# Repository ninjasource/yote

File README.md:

# Yote - Year of the Ear

Experiments with the nrf5340 Audio Dk, CS47L63 DSP chip and Yote experimental hearing aid. 
For Rust firmware, open the `firmware` folder instead of working from this folder

## Prerequisites

`cargo install probe-rs --features="cli"`

If probe-rs does not work then a known working version can be found here:
https://github.com/probe-rs/probe-rs.git#ff2370fb

## To run

NOTE on naming:
All the examples prefixed with "yote" are for the custom built hearing aid device. Everything else is for the nRF5340 Audio-dk

IMPORTANT: be sure to set the appropriate runner in .cargo/config.toml

```
cargo run --bin blinky --release
```

## Troubleshooting

You may get an "Arm specific error at runtime and the most likely cause is that you ran probe-run with the `--erase-all` flag set.
Check the notes in `.cargo/config.toml`

Here are some commands you may find useful when working with the nrf5340 audio dk. 
You will need to install the nrfjprog command line tools from Nordic beforehand.

```
nrfjprog -i
nrfjprog --eraseall --snr 1050175639 (locks up)
nrfjprog --recover --coprocessor CP_APPLICATION --snr 1050175639
nrfjprog --recover --snr 1050175639 (same as application above)
nrfjprog --recover --coprocessor CP_NETWORK --snr 1050175639 (locks up)
```

Here is some code that you can use to flash the device without probe-run:

```
#! /usr/bin/env bash

cargo objcopy --release -- -O ihex test.hex
nrfjprog -f NRF53 --erasepage 0x00000000-0x00100000
nrfjprog -f NRF53 --program test.hex --debugreset
rm test.hex
```

## How it works

This demo uses the mcu to generate a tone and plays it into the cs47l63 dsp chip. 
Before it can do that it has to configure the dsp chip correctly by writing to various registers over spi.
There are multiple tasks running simultaneously so we need a mechanism to share the spi bus between them.

The demo runs three main tasks simultaneously: 
1. Handle interrupts from the DSP chip which indicates that long running tasks on the DSP have been completed
2. Handle button presses to control playback and volume
3. Generate a waveform in real time and push the data to the DSP chip over the I2S sound bus

## Project structure

The `cs47l63` cargo library is responsible for booting up the cs47l63 chip correctly and providing a bunch of register address and constants to be used by the application.
The `hw_dsp` (hardware digital signal processing) constrains a collection of helper functions that make calls to the `cs47l63` driver to configure it.
The `main.rs` application should use `dsp` module to exclusively communicate with the `cs47l63` even though, in theory, it could communicate directly with it through the `shared_bus` module. Right now there is some code duplication because of some power saving experiments where we need to drop the spi bus after every use. The duplicated code should be consolidated as soon as an acceptable abstraction has been designed.

## Chapro compilation

CC=arm-none-eabi-gcc
AR=arm-none-eabi-ar
CFLAGS = -W -Wall -Os -mthumb -ffunction-sections -fdata-sections -mcpu=cortex-m33 -DBR_ARMEL_CORTEXM_GCC -I$(INCDIR) -Wno-unused-local-typedef -fPIC -mfpu=fpv5-sp-d16 -mfloat-abi=hard

## Notes on Power Consumption

Here are some of the things that seem to affect power consumption:

Logging: No effect unless a debugger is attached - then huge effect
Core clock 64Mhz -> 128Mhz and Flash Cache enabled - 200uA consumption
Setting all peripheral pins to Input Low on startup - no effect, they seem to already default to their lowest power setting anyway

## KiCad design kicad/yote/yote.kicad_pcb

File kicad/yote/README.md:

# Kicad project for schematic and PCB

Requires Kicad 8.0
Step files for the 3D rendering of the board will be checked in soon but at the moment they are not in the project path and therefore not rendered correctly. 
This messes up the PCB Design Rule checker too. Kicad projects are a little tricky to setup to work on multiple machines because of all the internal and external library files involved. 

If you do not have the correct version of Kicad installed then you can use the exported PDF schematic below:

Please see output/yote.pdf for now

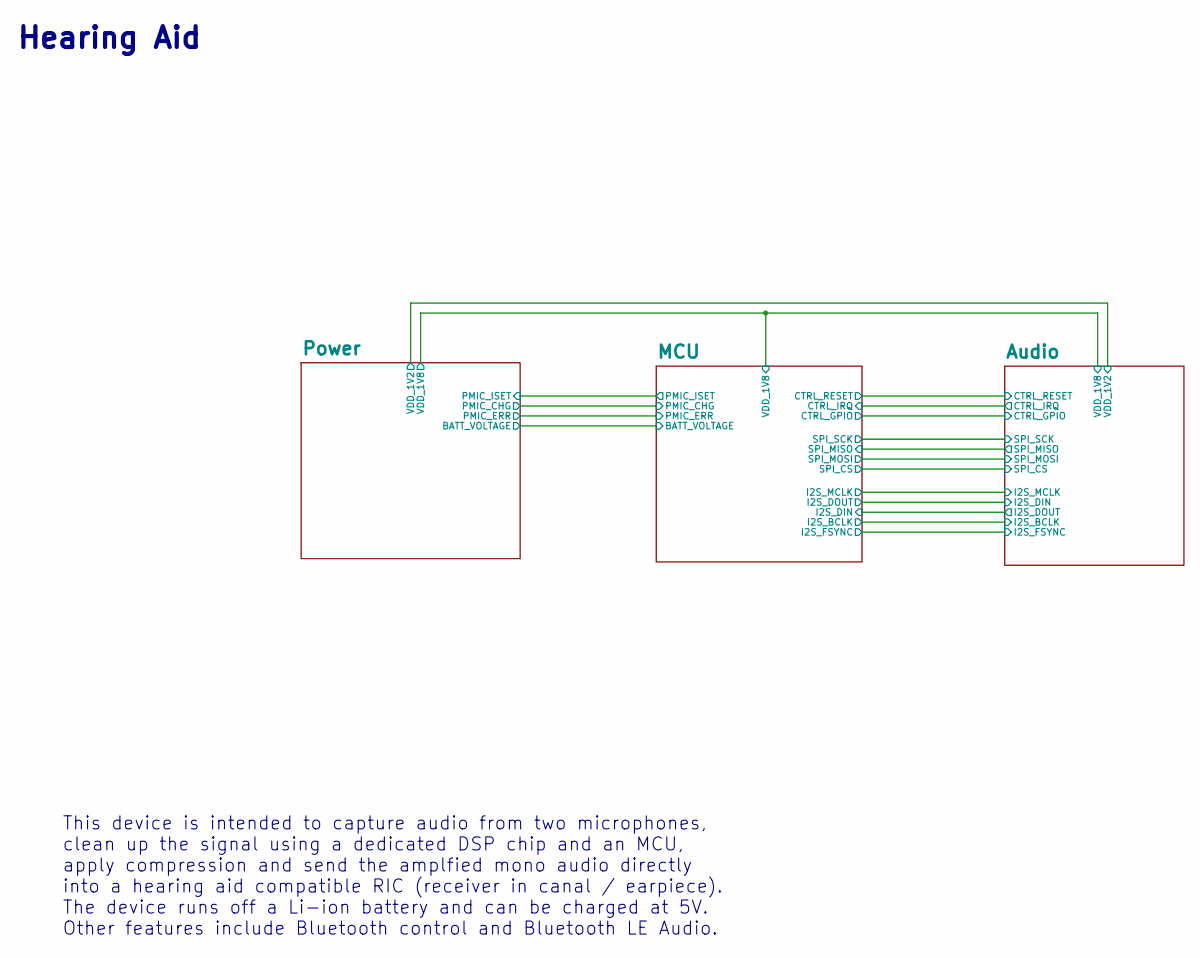
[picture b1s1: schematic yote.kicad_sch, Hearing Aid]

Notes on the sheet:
Hearing Aid
This device is intended to capture audio from two microphones, clean up the signal using a dedicated DSP chip and an MCU, apply compression and send the amplfied mono audio directly into a hearing aid compatible RIC (receiver in canal / earpiece). The device runs off a Li-ion battery and can be cha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

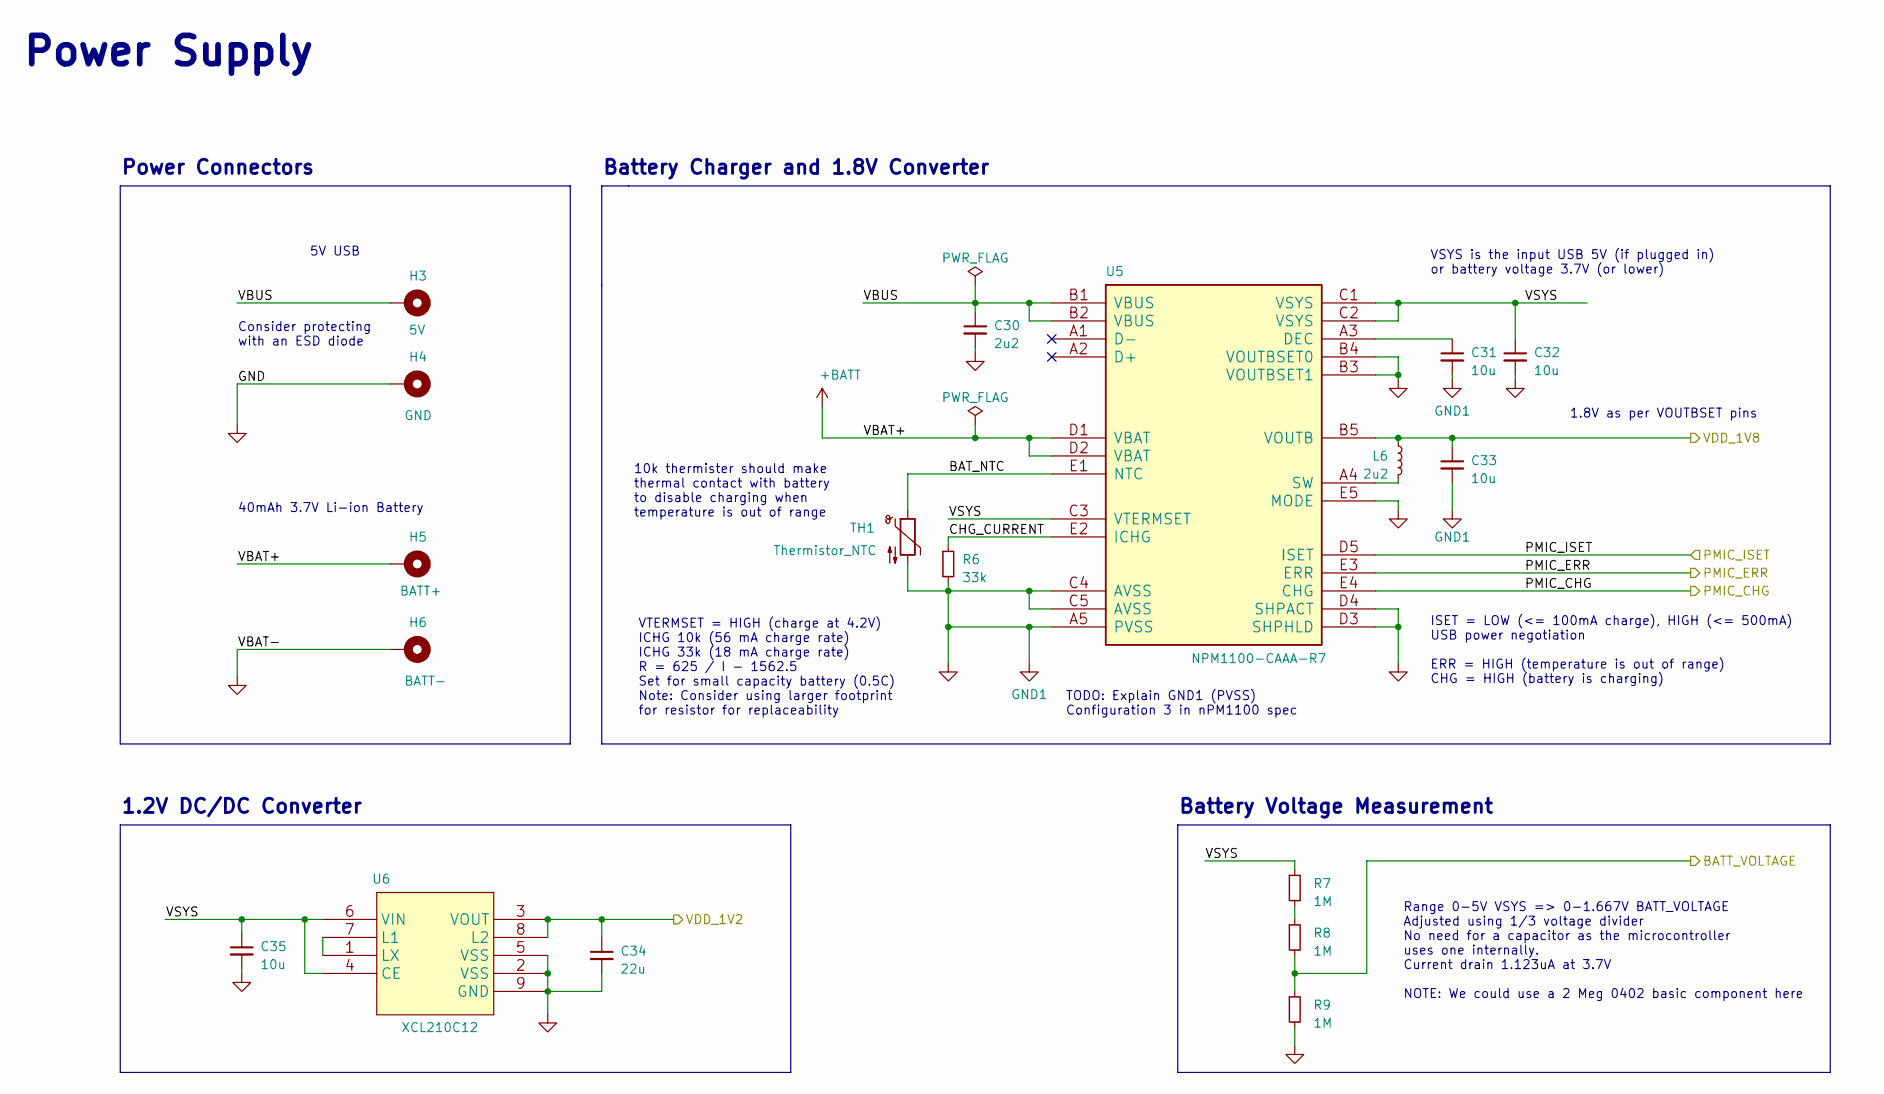
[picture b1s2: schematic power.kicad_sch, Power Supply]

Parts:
C30: 2u2; C_0402_1005Metric_Square; Mfg Part # GRM155R61A225KE95D
C31, C32, C33, C35: 10u; C_0603_1608Metric_Square; Mfg Part # GRM188R61A106KE69D
C34: 22u; C_0603_1608Metric_Square; Mfg Part # GRM188R61A226ME15D
H3: 5V; MountingHole_0.6mm_Pad_TopBottom
H4: GND; MountingHole_0.6mm_Pad_TopBottom
H5: BATT+; MountingHole_0.6mm_Pad_TopBottom
H6: BATT-; MountingHole_0.6mm_Pad_TopBottom
L6: 2u2; L_0603_1608Metric_MLZ1608M100WTD25; Mfg Part # MLP1608H2R2BT0S1
R6: 33k; R_0603_1608Metric_Square; Mfg Part # 0603WAF3302T5E
R7, R8, R9: 1M; R_0201_0603Metric_Square; Mfg Part # RC0201FR-071ML
TH1: Thermistor_NTC; R_0402_1005Metric_Square; Mfg Part # NCU15XH103F6SRC
U5: NPM1100-CAAA-R7; PARTREV V1.0
U6: XCL210C12; Mfg Part # XCL210C121GR-G

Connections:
+1V8: C33.1, L6.2, U5.B5 (VOUTB); also elsewhere on the board
+BATT: H5.1, U5.D1 (VBAT), U5.D2 (VBAT); also elsewhere on the board
/Audio/VDD_1V2: C34.1, U6.3 (VOUT), U6.8 (L2); also elsewhere on the board
/MCU/BATT_VOLTAGE: R8.2, R9.1; also elsewhere on the board
/MCU/PMIC_CHG: U5.E4 (CHG); also elsewhere on the board
/MCU/PMIC_ERR: U5.E3 (ERR); also elsewhere on the board
/MCU/PMIC_ISET: U5.D5 (ISET); also elsewhere on the board
/Power/BAT_NTC: TH1.1, U5.E1 (NTC)
/Power/CHG_CURRENT: R6.1, U5.E2 (ICHG)
/Power/VBUS: C30.1, H3.1, U5.B1 (VBUS), U5.B2 (VBUS)
/Power/VSYS: C32.1, C35.1, R7.1, U5.C1 (VSYS), U5.C2 (VSYS), U5.C3 (VTERMSET), U6.4 (CE), U6.6 (VIN)
GND: C30.2, C31.2, C32.2, C33.2, C34.2, C35.2, H4.1, H6.1, R6.2, R9.2, TH1.2, U5.A5 (PVSS), U5.B3 (VOUTBSET1), U5.B4 (VOUTBSET0), U5.C4 (AVSS), U5.C5 (AVSS), U5.D3 (SHPHLD), U5.D4 (SHPACT), U5.E5 (MODE), U6.2 (VSS), U6.5 (VSS), U6.9 (GND); also elsewhere on the board
unnamed: R7.2, R8.1
unnamed: C31.1, U5.A3 (DEC)
unnamed: L6.1, U5.A4 (SW)
unnamed: U6.1 (LX), U6.7 (L1)

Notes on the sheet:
VSYS is the input USB 5V (if plugged in) or battery voltage 3.7V (or lower)
Range 0-5V VSYS => 0-1.667V BATT_VOLTAGE Adjusted using 1/3 voltage divider No need for a capacitor as the microcontroller uses one internally. Current drain 1.123uA at 3.7V NOTE: We could use a 2 Meg 0402 basic component here
TODO: Explain GND1 (PVSS) Configuration 3 in nPM1100 spec
Battery Voltage Measurement
Battery Charger and 1.8V Converter
ISET = LOW (<= 100mA charge), HIGH (<= 500mA) USB power negotiation ERR = HIGH (temperature is out of range) CHG = HIGH (battery is charging)
1.2V DC/DC Converter
1.8V as per VOUTBSET pins
5V USB
Power Supply
40mAh 3.7V Li-ion Battery
Consider protecting with an ESD diode
VTERMSET = HIGH (charge at 4.2V) ICHG 10k (56 mA charge rate) ICHG 33k (18 mA charge rate) R = 625 / I - 1562.5 Set for small capacity battery (0.5C) Note: Consider using larger footprint for resistor for replaceability
Power Connectors
10k thermister should make thermal contact with battery to disable charging when temperature is out of range

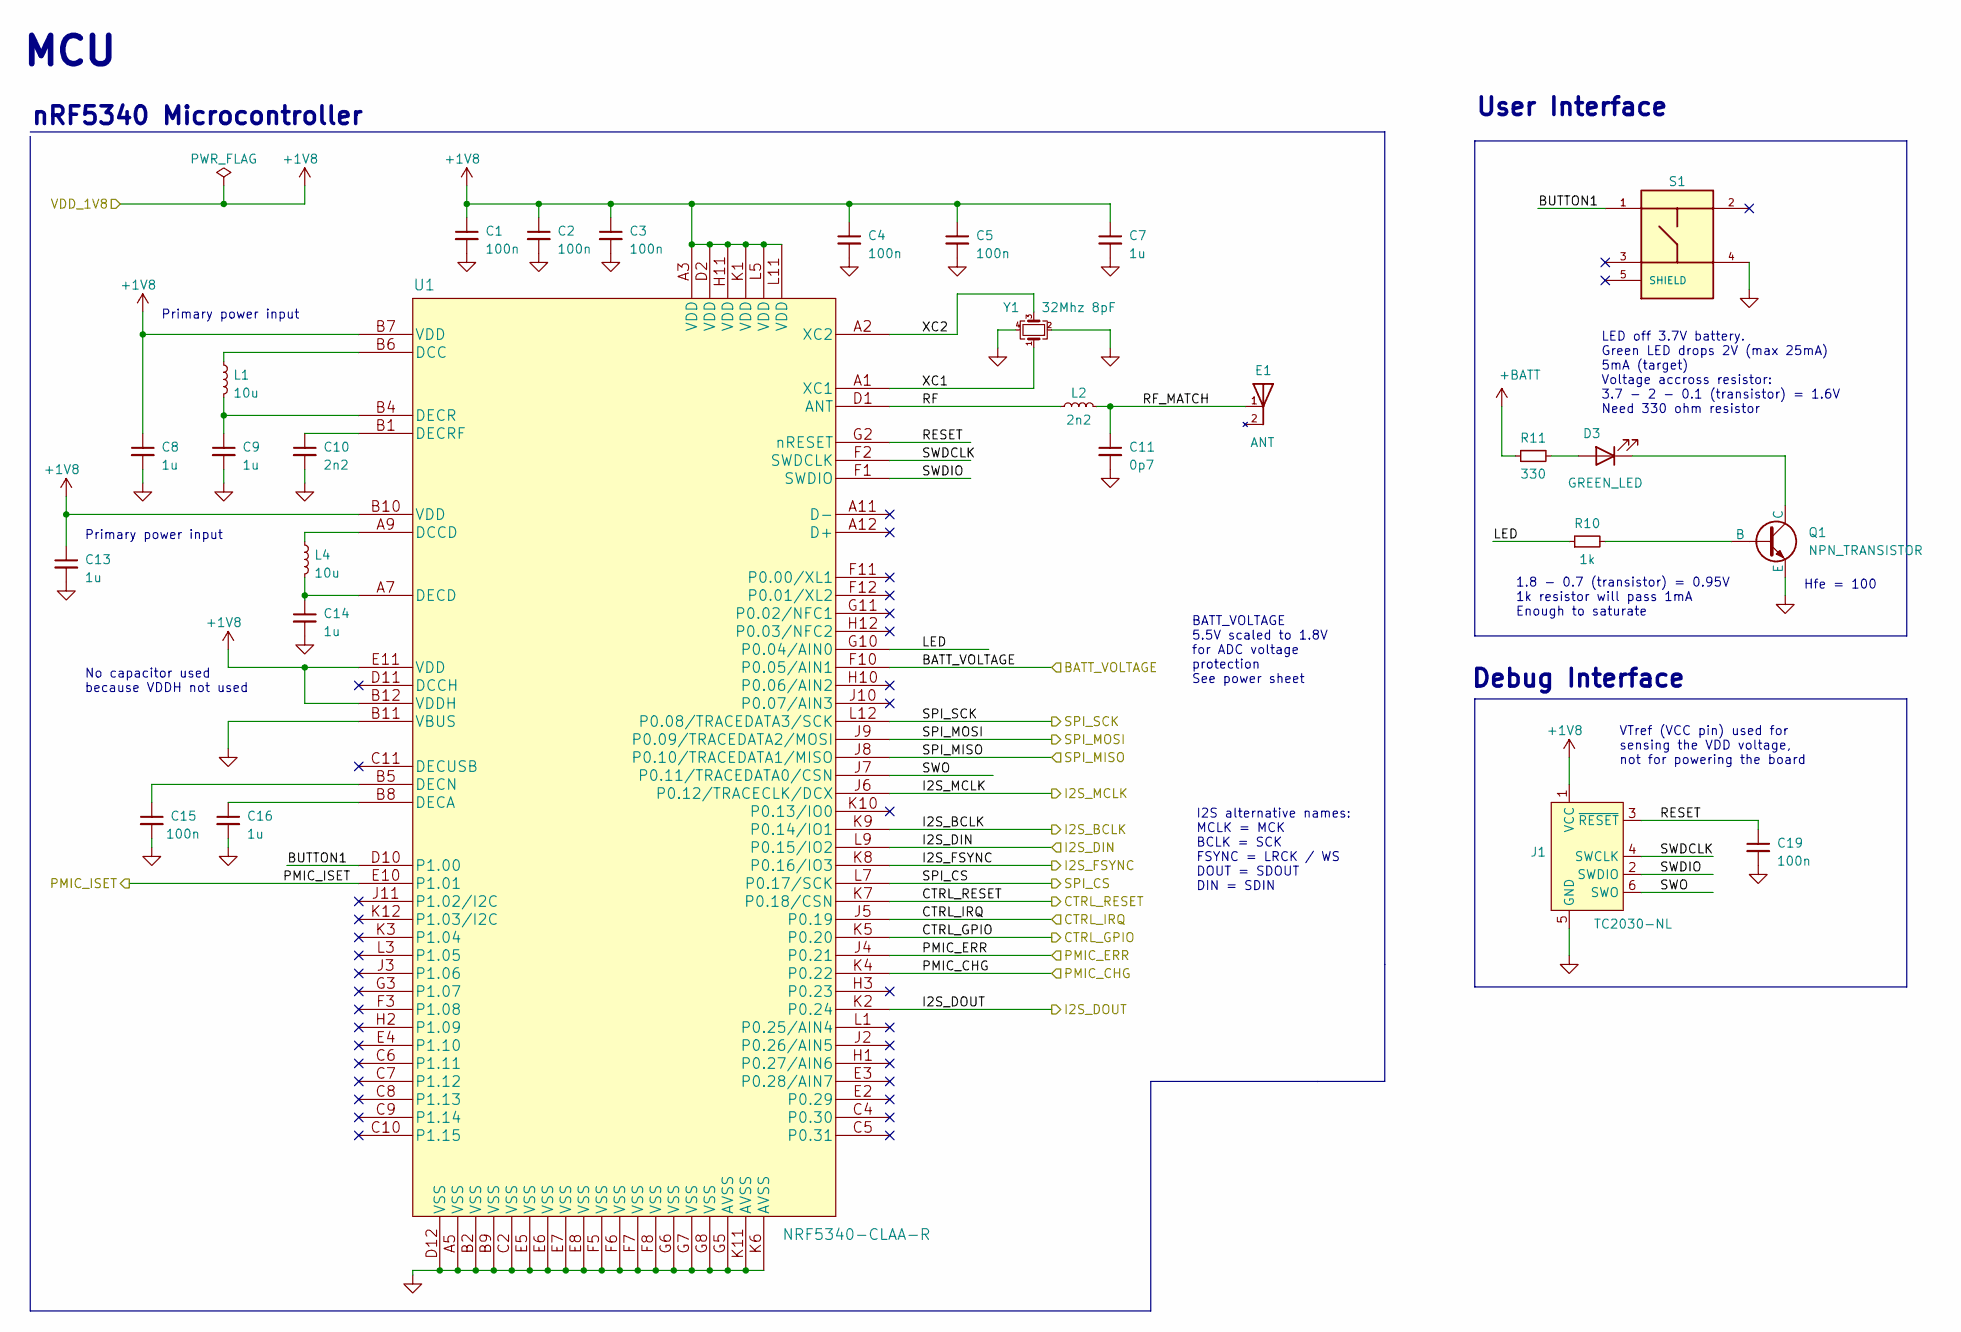
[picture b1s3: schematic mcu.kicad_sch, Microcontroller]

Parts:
C1, C2, C3, C4, C5, C15, C19: 100n; C_0201_0603Metric_Square; Mfg Part # GRM033R61A104KE15D
C7, C8, C9, C13, C14, C16: 1u; C_0402_1005Metric_Square; Mfg Part # GRM155R60J105KE19D
C10: 2n2; C_0201_0603Metric_Square; Mfg Part # GRM033R71A222KA01D
C11: 0p7; C_0201_0603Metric_Square; Mfg Part # GRM0335C1HR70WA01D
D3: GREEN_LED; LED_0402_1005Metric; Mfg Part # 16-213SYGC/S530-E3/TR8
E1: ANT; 2450AT18B100E; PARTREV 4.0
J1: TC2030-NL; Tag-Connect_TC2030-IDC-NL_2x03_P1.27mm_Vertical
L1, L4: 10u; L_0603_1608Metric_MLZ1608M100WTD25; Mfg Part # MLZ1608M100WTD25
L2: 2n2; L_0201_0603Metric_Square; Mfg Part # LQP03HQ2N2B02
Q1: NPN_TRANSISTOR; Npn_Transistor_TP5001P3; Mfg Part # TP5001P3
R10: 1k; R_0201_0603Metric_Square; Mfg Part # RC0201FR-071KL
R11: 330; R_0201_0603Metric_Square; Mfg Part # RC0201FR-07330RL
S1: PUSH_BTN; SW_PTS840GMSMTRLFS; Mfg Part # PTS840GMSMTRLFS
U1: NRF5340-CLAA-R; Mfg Part # NRF5340-CLAA
Y1: 32Mhz 8pF; MP06003_Crystal; Mfg Part # CX2016DB32000D0WZRC1

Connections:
+1V8: C1.1, C2.1, C3.1, C4.1, C5.1, C7.1, C8.1, C13.1, J1.1 (VCC), U1.A3 (VDD), U1.B7 (VDD), U1.B10 (VDD), U1.B12 (VDDH), U1.D2 (VDD), U1.E11 (VDD), U1.H11 (VDD), U1.K1 (VDD), U1.L5 (VDD), U1.L11 (VDD); also elsewhere on the board
+BATT: R11.1; also elsewhere on the board
/Audio/CTRL_GPIO: U1.K5 (P0.20); also elsewhere on the board
/Audio/CTRL_IRQ: U1.J5 (P0.19); also elsewhere on the board
/Audio/CTRL_RESET: U1.K7 (P0.18/CSN); also elsewhere on the board
/Audio/I2S_BCLK: U1.K9 (P0.14/IO1); also elsewhere on the board
/Audio/I2S_DIN: U1.K2 (P0.24); also elsewhere on the board
/Audio/I2S_DOUT: U1.L9 (P0.15/IO2); also elsewhere on the board
/Audio/I2S_FSYNC: U1.K8 (P0.16/IO3); also elsewhere on the board
/Audio/I2S_MCLK: U1.J6 (P0.12/TRACECLK/DCX); also elsewhere on the board
/Audio/SPI_CS: U1.L7 (P0.17/SCK); also elsewhere on the board
/Audio/SPI_MISO: U1.J8 (P0.10/TRACEDATA1/MISO); also elsewhere on the board
/Audio/SPI_MOSI: U1.J9 (P0.09/TRACEDATA2/MOSI); also elsewhere on the board
/Audio/SPI_SCK: U1.L12 (P0.08/TRACEDATA3/SCK); also elsewhere on the board
/MCU/BATT_VOLTAGE: U1.F10 (P0.05/AIN1); also elsewhere on the board
/MCU/BUTTON1: S1.1, U1.D10 (P1.00)
/MCU/LED: R10.1, U1.G10 (P0.04/AIN0)
/MCU/PMIC_CHG: U1.K4 (P0.22); also elsewhere on the board
/MCU/PMIC_ERR: U1.J4 (P0.21); also elsewhere on the board
/MCU/PMIC_ISET: U1.E10 (P1.01); also elsewhere on the board
/MCU/RESET: C19.1, J1.3 (~RESET), U1.G2 (nRESET)
/MCU/RF: L2.1, U1.D1 (ANT)
/MCU/RF_MATCH: C11.1, E1.1, L2.2
/MCU/SWDCLK: J1.4 (SWCLK), U1.F2 (SWDCLK)
/MCU/SWDIO: J1.2 (SWDIO), U1.F1 (SWDIO)
/MCU/SWO: J1.6 (SWO), U1.J7 (P0.11/TRACEDATA0/CSN)
/MCU/XC1: U1.A1 (XC1), Y1.1
/MCU/XC2: U1.A2 (XC2), Y1.3
GND: C1.2, C2.2, C3.2, C4.2, C5.2, C7.2, C8.2, C9.2, C10.2, C11.2, C13.2, C14.2, C15.2, C16.2, C19.2, J1.5 (GND), Q1.3 (E), S1.4, U1.A5 (VSS), U1.B2 (VSS), U1.B9 (VSS), U1.B11 (VBUS), U1.C2 (VSS), U1.D12 (VSS), U1.E5 (VSS), U1.E6 (VSS), U1.E7 (VSS), U1.E8 (VSS), U1.F5 (VSS), U1.F6 (VSS), U1.F7 (VSS), U1.F8 (VSS), U1.G5 (AVSS), U1.G6 (VSS), U1.G7 (VSS), U1.G8 (VSS), U1.K6 (AVSS), U1.K11 (AVSS), Y1.2, Y1.4; also elsewhere on the board
unnamed: D3.2 (A), R11.2
unnamed: D3.1 (K), Q1.1 (C)
unnamed: Q1.2 (B), R10.2
unnamed: L1.1, U1.B6 (DCC)
unnamed: L4.1, U1.A9 (DCCD)
unnamed: C16.1, U1.B8 (DECA)
unnamed: C14.1, L4.2, U1.A7 (DECD)
unnamed: C15.1, U1.B5 (DECN)
unnamed: C9.1, L1.2, U1.B4 (DECR)
unnamed: C10.1, U1.B1 (DECRF)

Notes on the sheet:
LED off 3.7V battery. Green LED drops 2V (max 25mA) 5mA (target) Voltage accross resistor: 3.7 - 2 - 0.1 (transistor) = 1.6V Need 330 ohm resistor
BATT_VOLTAGE 5.5V scaled to 1.8V for ADC voltage protection See power sheet
VTref (VCC pin) used for sensing the VDD voltage, not for powering the board
1.8 - 0.7 (transistor) = 0.95V 1k resistor will pass 1mA Enough to saturate
I2S alternative names: MCLK = MCK BCLK = SCK FSYNC = LRCK / WS DOUT = SDOUT DIN = SDIN
No capacitor used because VDDH not used
MCU
Debug Interface
Primary power input
Hfe = 100
User Interface
nRF5340 Microcontroller

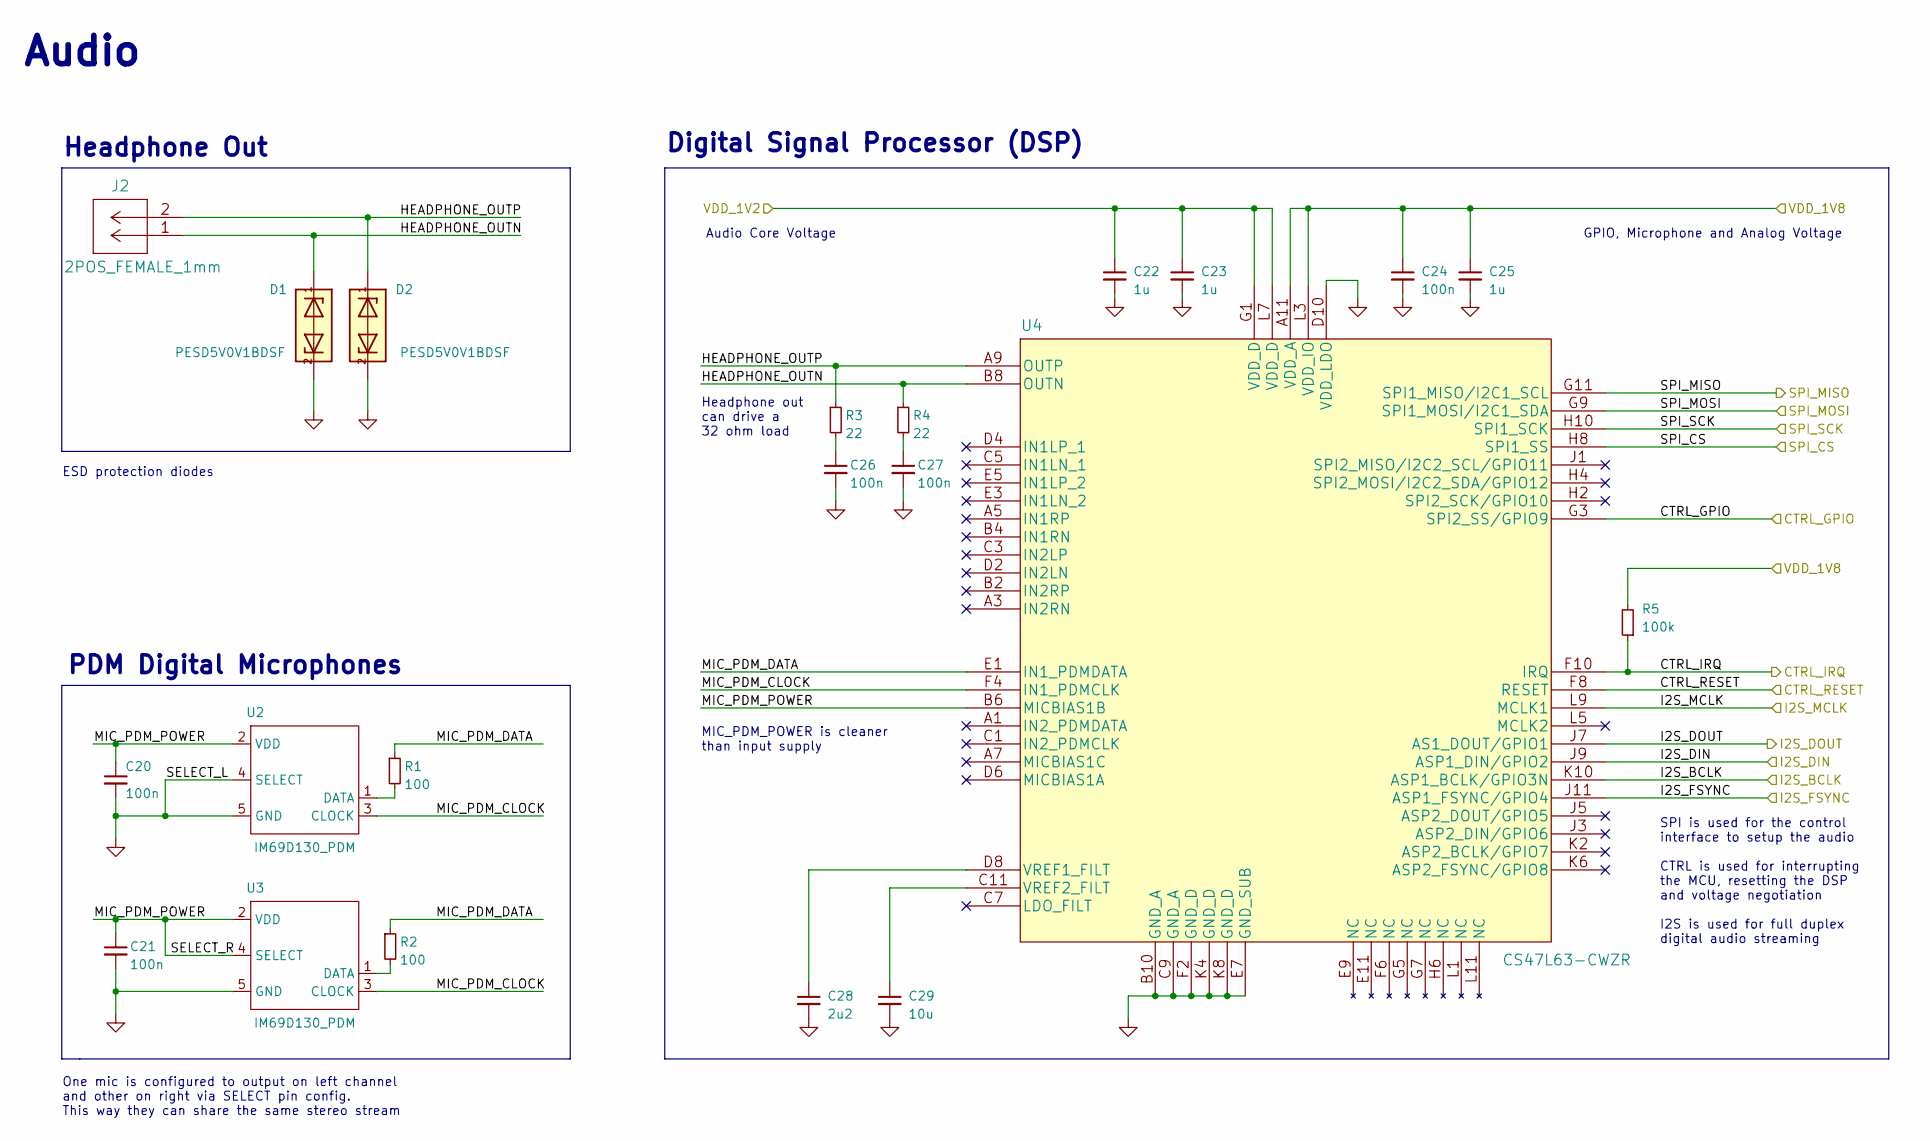
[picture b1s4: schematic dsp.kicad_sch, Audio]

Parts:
C20, C21, C24, C26, C27: 100n; C_0201_0603Metric_Square; Mfg Part # GRM033R61A104KE15D
C22, C23, C25: 1u; C_0402_1005Metric_Square; Mfg Part # GRM155R60J105KE19D
C28: 2u2; C_0402_1005Metric_Square; Mfg Part # GRM155R61A225KE95D
C29: 10u; C_0603_1608Metric_Square; Mfg Part # GRM188R61A106KE69D
D1, D2: PESD5V0V1BDSF; D_0603_1608Metric_Square; Mfg Part # PESD5V0V1BDSF,315
J2: 2POS_FEMALE_1mm; BC075-02-A-L-A; Mfg Part # BC075-02-A-L-A
R1, R2: 100; R_0201_0603Metric_Square; Mfg Part # RC0201FR-07100RL
R3, R4: 22; R_0201_0603Metric_Square; Mfg Part # RC0201FR-0722RL
R5: 100k; R_0201_0603Metric_Square; Mfg Part # RC0201FR-07100KL
U2, U3: IM69D130_PDM; MIC_IM69D130V01XTSA1_PadFix_Round; Mfg Part # IM69D130V01XTSA1
U4: CS47L63-CWZR; Mfg Part # CS47L63-CWZR

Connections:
+1V8: C24.1, C25.1, R5.2, U4.A11 (VDD_A), U4.L3 (VDD_IO); also elsewhere on the board
/Audio/CTRL_GPIO: U4.G3 (SPI2_SS/GPIO9); also elsewhere on the board
/Audio/CTRL_IRQ: R5.1, U4.F10 (IRQ); also elsewhere on the board
/Audio/CTRL_RESET: U4.F8 (RESET); also elsewhere on the board
/Audio/HEADPHONE_OUTN: D1.1, J2.1, R4.1, U4.B8 (OUTN)
/Audio/HEADPHONE_OUTP: D2.1, J2.2, R3.1, U4.A9 (OUTP)
/Audio/I2S_BCLK: U4.K10 (ASP1_BCLK/GPIO3N); also elsewhere on the board
/Audio/I2S_DIN: U4.J9 (ASP1_DIN/GPIO2); also elsewhere on the board
/Audio/I2S_DOUT: U4.J7 (AS1_DOUT/GPIO1); also elsewhere on the board
/Audio/I2S_FSYNC: U4.J11 (ASP1_FSYNC/GPIO4); also elsewhere on the board
/Audio/I2S_MCLK: U4.L9 (MCLK1); also elsewhere on the board
/Audio/MIC_PDM_CLOCK: U2.3 (CLOCK), U3.3 (CLOCK), U4.F4 (IN1_PDMCLK)
/Audio/MIC_PDM_DATA: R1.1, R2.1, U4.E1 (IN1_PDMDATA)
/Audio/MIC_PDM_POWER: C20.1, C21.1, U2.2 (VDD), U3.2 (VDD), U3.4 (SELECT), U4.B6 (MICBIAS1B)
/Audio/SPI_CS: U4.H8 (SPI1_SS); also elsewhere on the board
/Audio/SPI_MISO: U4.G11 (SPI1_MISO/I2C1_SCL); also elsewhere on the board
/Audio/SPI_MOSI: U4.G9 (SPI1_MOSI/I2C1_SDA); also elsewhere on the board
/Audio/SPI_SCK: U4.H10 (SPI1_SCK); also elsewhere on the board
/Audio/VDD_1V2: C22.1, C23.1, U4.G1 (VDD_D), U4.L7 (VDD_D); also elsewhere on the board
GND: C20.2, C21.2, C22.2, C23.2, C24.2, C25.2, C26.2, C27.2, C28.2, C29.2, D1.2, D2.2, U2.4 (SELECT), U2.5 (GND), U3.5 (GND), U4.B10 (GND_A), U4.C9 (GND_A), U4.D10 (VDD_LDO), U4.E7 (GND_SUB), U4.F2 (GND_D), U4.K4 (GND_D), U4.K8 (GND_D); also elsewhere on the board
unnamed: C26.1, R3.2
unnamed: C27.1, R4.2
unnamed: R1.2, U2.1 (DATA)
unnamed: R2.2, U3.1 (DATA)
unnamed: C28.1, U4.D8 (VREF1_FILT)
unnamed: C29.1, U4.C11 (VREF2_FILT)

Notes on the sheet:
Digital Signal Processor (DSP)
One mic is configured to output on left channel and other on right via SELECT pin config. This way they can share the same stereo stream
SPI is used for the control interface to setup the audio CTRL is used for interrupting the MCU, resetting the DSP and voltage negotiation I2S is used for full duplex digital audio streaming
GPIO, Microphone and Analog Voltage
Audio Core Voltage
Audio
Headphone out can drive a 32 ohm load
Headphone Out
ESD protection diodes
MIC_PDM_POWER is cleaner than input supply
PDM Digital Microphones

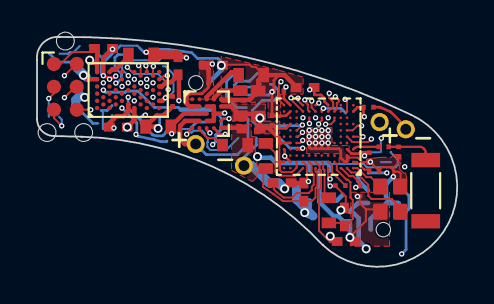
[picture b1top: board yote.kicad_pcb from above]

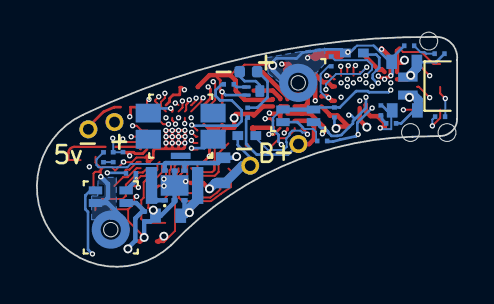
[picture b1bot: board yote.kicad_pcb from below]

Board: 8 copper layers, 23.4 x 12.8 mm, 66 parts (28 on the bottom side), 59 nets.

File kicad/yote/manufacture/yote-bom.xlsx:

|  |  | YOTE – Bill of Materials
Item # | *Designator | *Qty | Manufacturer | *Mfg Part # | Description / Value | *Package/Footprint | Type | Your Instructions / Notes
1 | C1, C2, C3, C4, C5, C15, C19, C20, C21, C24, C26, C27 | 12 | Murata Electronics | GRM033R61A104KE15D | 100n | 0201 |  | Capacitor, X5R, ±10%
2 | C7, C8, C9, C13, C14, C16, C22, C23, C25 | 9 | Murata Electronics | GRM155R60J105KE19D | 1u | 0402 |  | Capacitor, X5R, ±10%, 6.3V
3 | C10 | 1 | Murata Electronics | GRM033R71A222KA01D | 2n2 | 0201 |  | Capacitor, X7R, ±10%, 10V
4 | C11 | 1 | Murata Electronics | GRM0335C1HR70WA01D | 0p7 | 0201 |  | Capacitor, NP0, ±0.1pF
5 | C28, C30 | 2 | Murata Electronics | GRM155R61A225KE95D | 2u2 | 0402 |  | Capacitor, X5R, ±20%
6 | C29, C31, C32, C33, C35 | 5 | Murata Electronics | GRM188R61A106KE69D | 10u | 0603 |  | Capacitor, Ceramic, X5R, ±20%, 10V
7 | C34 | 1 | Murata Electronics | GRM188R61A226ME15D | 22u | 0603 |  | Capacitor, X5R, ±20%, 6.3V
8 | D1, D2 | 2 | Nexperia | PESD5V0V1BDSF,315 | PESD5V0V1BDSF | 0603 |  | Very low capacitance bidirectional ESD protection diode
9 | D3 | 1 | Everlight Elec | 16-213SYGC/S530-E3/TR8 | GREEN_LED | 0402 |  | Green LED 2V forward voltage 25mA max
10 | E1 | 1 | Johanson Technology | 2450AT18B100E | ANT | SMD |  | 2.45 GHz chip antenna
11 | H3 | 1 |  |  | 5V | DNS |  | Footprint only – Do not place
12 | H4 | 1 |  |  | GND | DNS |  | Footprint only – Do not place
13 | H5 | 1 |  |  | BATT+ | DNS |  | Footprint only – Do not place
14 | H6 | 1 |  |  | BATT- | DNS |  | Footprint only – Do not place
15 | J1 | 1 |  |  | TC2030-NL | DNS |  | Footprint only – Do not place
16 | J2 | 1 | GCT | BC075-02-A-L-A | 2POS_FEMALE_1mm | SMD |  | 2POS 1.0MM PITCH SOCKET, SIL, SM
17 | L1, L4 | 2 | TDK | MLZ1608M100WTD25 | 10u | 0603 |  | Inductor, 250mA, ±20%, 1.05ohm. -55°C ~ 125°C
18 | L2 | 1 | Murata Electronics | LQP03HQ2N2B02 | 2n2 | 0201 |  | Inductor, 600mA, ±0.1ｎH, 120mOhm
19 | L6 | 1 | TDK | MLP1608H2R2BT0S1 | 2u2 | 0603 |  | 750mA 2.2uH ±20% 390mΩ 0603 Inductors
20 | Q1 | 1 | Tech Public | TP5001P3 | NPN_TRANSISTOR | SMD |  | NPN Transistor of with Hfe of around 100 for LED
21 | R1, R2 | 2 | YAGEO | RC0201FR-07100RL | 100 | 0201 |  | Resistor
22 | R3, R4 | 2 | YAGEO | RC0201FR-0722RL | 22 | 0201 |  | Resistor
23 | R5 | 1 | YAGEO | RC0201FR-07100KL | 100k | 0201 |  | Resistor
24 | R6 | 1 | UNI-ROYAL | 0603WAF3302T5E | 33k | 0603 |  | Resistor
25 | R7, R8, R9 | 3 | YAGEO | RC0201FR-071ML | 1M | 0201 |  | Resistor
26 | R10 | 1 | YAGEO | RC0201FR-071KL | 1k | 0201 |  | Resistor
27 | R11 | 1 | YAGEO | RC0201FR-07330RL | 330 | 0201 |  | Resistor
28 | S1 | 1 | C&K | PTS840GMSMTRLFS | PUSH_BTN | SMD |  | Push button sideways switch
29 | TH1 | 1 | Murata Electronics | NCU15XH103F6SRC | Thermistor_NTC | 0402 |  | 10k 0.1mA ±1% 3380K ±1% 0402 NTC Thermistor
30 | U1 | 1 | Nordic Semiconductor | NRF5340-CLAA | NRF5340-CLAA-R | SMD |  | nRF5340 microcontroller
31 | U2, U3 | 2 | Infineon Technologies | IM69D130V01XTSA1 | IM69D130_PDM | SMD |  | IM69D130 PDM microphone
32 | U4 | 1 | Cirrus Logic | CS47L63-CWZR | CS47L63-CWZR | SMD |  | CS47L63 digital signal processing IC
33 | U5 | 1 | Nordic Semiconductor | NPM1100-CAAA | NPM1100-CAAA-R7 | SMD |  | nPM1100 battery charger
34 | U6 | 1 | Torex Semiconductor | XCL210C121GR-G | XCL210C12 | SMD |  | 1_2V dcdc converter
35 | Y1 | 1 | Kyocera | CX2016DB32000D0WZRC1 | 32Mhz 8pF | CX2016 |  | Four pin crystal, GND on pins 2 and 4, small symbol, 32mhs 8pF

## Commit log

2024-03-28 Updated schematic export and added readme
2024-03-31 Added more instructions to readme

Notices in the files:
parts and their libraries:
Copyright 2021 Accelerated Designs. All rights reserved.
